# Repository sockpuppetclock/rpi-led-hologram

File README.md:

Holographic Display
==================================================
This fork adds LED controller scripts for use with a 64x64 HUB75 LED matrix as a volumetric display.
 * `startup.sh` (starts holographic-viewer, useful if set to start after boot)
 * `utils/holographic-viewer.cc` (main LED driving script)
 * `utils/holo-controller.py` & `utils/holo-autocontrol.py` (control display via zeromq)
 * `utils/img2anim.cc` (script to create .anim files from 64x64 images for holographic-viewer)

 ```bash
apt install make cmake g++ graphicsmagick-libmagick-dev-compat cppzmq-dev python3-zmq
```

Build before running:
 ```bash
 make -C utils
 make -C examples-api-use
 ```

Controlling RGB LED display with Raspberry Pi GPIO
==================================================

A library to control commonly available 64x64, 32x32 or 16x32 RGB LED panels
with the Raspberry Pi. Can support PWM up to 11Bit per channel, providing
true 24bpp color with CIE1931 profile.

Supports 3 chains with many panels each on a regular Pi.
On a Raspberry Pi 2 or 3, you can easily chain 12 panels in that chain
(so 36 panels total), but you can theoretically stretch that to up
to 96-ish panels (32 chain length) and still reach
around 100Hz refresh rate with full 24Bit color (theoretical - never tested
this; there might likely be timing problems with the panels that will creep
up then).

With fewer colors or so-called 'outdoor panels' you can control even more,
faster.

The LED-matrix library is (c) Henner Zeller <h.zeller@acm.org>, licensed with
[GNU General Public License Version 2.0 (or any later version)](http://www.gnu.org/licenses/gpl-2.0.txt)
(which means, if you use it in a product somewhere, you need to make the
source and all your modifications available to the receiver of such product so
that they have the freedom to adapt and improve). 
Yes, you are also allowed to use
this code under the [GNU General Public License Version 3.0](http://www.gnu.org/licenses/gpl-3.0.txt) 
which allows linking with Apache 2.0 code and LGPL-3.0 code.

## Discourse discussion group

**If you'd like help, please do not file a bug, use the discussion board instead:**
https://rpi-rgb-led-matrix.discourse.group/  (obviously please read this whole page first).
If you file a bug asking for personal help instead of using the discourse group, please
state in your bug that you have read this entire page and that you're indeed filing a bug
or request for improvement. Otherwise, please use the discourse group.

Overview
--------
The RGB LED matrix panels can be scored at [Sparkfun][sparkfun],
[AdaFruit][ada] or eBay and Aliexpress. If you are in China, I'd try to get
them directly from some manufacturer, Taobao or Alibaba.

The `RGBMatrix` class provided in `include/led-matrix.h` does what is needed
to control these. You can use this as a library in your own projects or just
use the demo binary provided here which provides some useful examples.

Check out [utils/ directory for some ready-made tools](./utils) to get started
using the library, or the [examples-api-use/](./examples-api-use) directory if
you want to get started programming your own utils.

Raspberry Pi up to 4 supported
------------------------------

This library supports the old Raspberry Pi's Version 1 with 26 pin header and
also the B+ models, the Pi Zero, Raspberry Pi 2 and 3 with 40 pins, as well
as the Compute Modules which have 44 GPIOs.

The Raspberry Pi 5 still needs some research into the vastly changed peripherals
and is not yet supported. See https://github.com/hzeller/rpi-rgb-led-matrix/issues/1603#issuecomment-2624713250
and https://github.com/adafruit/Adafruit_Blinka_Raspberry_Pi5_Piomatter

The 26 pin models can drive one chain of RGB panels, the 40 pin models
**up to three** chains in parallel (each chain 12 or more panels long).
The Compute Module can drive **up to 6 chains in parallel**.
The Raspberry Pi 2 and 3 are faster and generally perferred to the older
models (and the Pi Zero). With the faster models, the panels sometimes
can't keep up with the speed; check out
this [troubleshooting section](#troubleshooting) what to do.

A lightweight, non-GUI, distribution such as [DietPi] is recommended.
[Raspbian Lite][raspbian-lite] is a bit easier to get started with and
is a good second choice.

Types of Displays
-----------------
There are various types of displays that come all with the same Hub75 connector.
They vary in the way the multiplexing is happening so this library supports
options to choose that.
All these are configured by flags (or, programmatically, in an [Options struct](include/led-matrix.h#L57)).

If you have a 64x32 display, you need to supply the flags
`--led-cols=64 --led-rows=32` for instance.

Depending on the Matrix, there are various configuration options that
you might need to set for it to work. See further below in the README for the
[detailed description of these](#changing-parameters-via-command-line-flags).
While the `--led-rows` and `--led-cols` can be derived from simply looking
at the panels, the other options might require some experimenting to find the
right setting if there is no description provided by the manufacturer of
the panel. Going through these options for experiments would typically not do
harm, so you're free to experiment to find your setting.

Flag                                | Description
:---------------      | :-----------------
`--led-cols`          | Columns in the LED matrix, the 'width'.
`--led-rows`          | Rows in the LED matrix, the 'height'.
`--led-multiplexing`  | In particular bright outdoor panels with small multiplex ratios require this. Often an indicator: if there are fewer address lines than expected: ABC (instead of ABCD) for 32 high panels and ABCD (instead of ABCDE) for 64 high panels.
`--led-row-addr-type` | Adressing of rows; in particular panels with only AB address lines might indicate that this is needed.
`--led-panel-type`    | Chipset of the panel. In particular if it doesn't light up at all, you might need to play with this option because it indicates that the panel requires a particular initialization sequence.

Panels can be chained by connecting the output of one panel to the input of
the next panel. You can chain quite a few together, but the refresh rate will
reduce with longer chains.

The 64x64 matrixes typically come in two kinds: with 5 address
lines (A, B, C, D, E), or (A, B); the latter needs a `--led-row-addr-type=1`
parameter. So-called 'outdoor panels' are typically brighter and allow for
faster refresh-rate for the same size, but do some multiplexing internally
of which there are a few types out there; they can be chosen with
the `--led-multiplexing` parameter.

There are some panels that have a different chip-set than the default HUB75.
These require some initialization sequence. The current supported types are
`--led-panel-type=FM6126A` and `--led-panel-type=FM6127`.

Generally, the higher scan-rate (e.g. 1:8), a.k.a. outdoor panels generally
allow faster refresh rate, but you might need to figure out the multiplexing
mapping if one of the three provided does not work.

Some 32x16 outdoor matrixes with 1:4 scan (e.g. [Qiangli Q10(1/4) or X10(1/4)](http://qiangliled.com/products-63.html))
have 4 address line (A, B, C, D). For such matrices is necessary to
use `--led-row-addr-type=2` parameter. Also the matrix Qiangli Q10(1/4)
have "Z"-stripe pixel mapping and in this case, you'd use two parameters
at the same time `--led-row-addr-type=2 --led-multiplexing=4`.

Let's do it
------------
This documentation is split into parts that help you through the process

  1. 
    [**Wire up the matrix to your Pi**](./wiring.md). This document describes
    what goes where. You might also be interested
    in [breakout boards](./adapter) for that.
    If you have an [Adafruit HAT] or [Adafruit Bonnet], you can choose that with
    a command line option [described below](#if-you-have-an-adafruit-hat-or-bonnet)
  2. Run a demo. You find that in the
     [examples-api-use/](./examples-api-use#running-some-demos) directory:
```
make -C examples-api-use
sudo examples-api-use/demo -D0
```
  3. Use the utilities. The [utils](./utils) directory has some ready-made
    useful utilities to show content. [Go there](./utils) to see how to
    compile and run these.
  4. Write your own programs using the Matrix in C++ or one of the
     bindings such as Python or C#.

### Wiring / Boards

Please see the [Adadpter Boards or Self Wiring](./adapter). 

Summary is:
- Yes you can self wire without level shifters and it will work most of the time, but if you're not in a hurry get a board
- https://www.electrodragon.com/product/rgb-matrix-panel-drive-board-for-raspberry-pi-v2/ **is the recommended solution with 3 channels and level shifters**. You can't go wrong there, but expect a bit of shipping time.
- If shipping time is crucial and you don't want to wire your own, Adafruit sells a single channel board (the electrodragon one is 3 channels), but note that its wiring is non standard and requires a special compile option or command line argument: https://www.adafruit.com/product/3211

### Utilities

The [utils directory](./utils) is meant for ready utilities to show images or
animated gifs or videos. Read the [README](./utils/README.md) there for
instructions how to compile.

There are external projects that use this library and provide higher level
network protocols, such as the
 * [FlaschenTaschen implementation](https://github.com/hzeller/flaschen-taschen)
   (VLC can send videos to it natively)
 * [PixelPusher implementation](https://github.com/hzeller/rpi-matrix-pixelpusher) (common in light art installations)
 * [ZeroMQ-server](https://github.com/Knifa/led-matrix-zmq-server) to receive
   content.
 * Marc's [FastLED_RPIRGBPanel_GFX](http://marc.merlins.org/perso/arduino/post_2020-01-01_Running-FastLED_-Adafruit_GFX_-and-LEDMatrix-code-on-High-Resolution-RGBPanels-with-a-Raspberry-Pi.html) allows running arduino code on linux/rPi and display on bigger RGBPanel matrices than arduino chips, can.

### API

The library comes as an API that you can use for your own utilities and use-cases.

  * The native library is a C++ library (see [include/](./include)).
    Example uses you find in the [examples-api-use/](./examples-api-use)
    directory.
  * If you prefer to program in C, there is also a
    [C API](./include/led-matrix-c.h).
  * In the [python](./bindings/python) subdirectory, you find a Python API including a
    couple of [examples](./bindings/python/samples) to get started.
  * There are a couple of external bindings, such as
      * [Nodejs binding] by Maxime Journaux
      * [Nodejs/Typescript binding] by Alex Eden
      * [Go binding] by Máximo Cuadros
      * [Rust binding] by Vincent Pasquier

### Changing parameters via command-line flags

For the programs in this distribution and also automatically in your own
programs using this library, there are a lot of parameters provided as command
line flags, so that you don't have to re-compile your programs to tweak them.
Some might need to be changed for your particular kind of panel.

Here is a little run-down of what these command-line flags do and when you'd
like to change them.

First things first: if you have a different wiring than described in
[wiring](./wiring.md), for instance if you have an Adafruit HAT/Bonnet, you can
choose these here:

```
--led-gpio-mapping=<gpio-mapping>: Name of GPIO mapping used. Default "regular"
```

This can have values such as
  - `--led-gpio-mapping=regular` The standard mapping of this library, described in the [wiring](./wiring.md) page.
  - `--led-gpio-mapping=adafruit-hat` The Adafruit HAT/Bonnet, that uses this library or
  - `--led-gpio-mapping=adafruit-hat-pwm` Adafruit HAT with the anti-flicker hardware mod [described below](#improving-flicker).
  - `--led-gpio-mapping=compute-module` Additional 3 parallel chains can be used with the Compute Module.

Learn more about the mappings in the [wiring documentation](wiring.md#alternative-hardware-mappings).

#### GPIO speed

```
--led-slowdown-gpio=<0..4>: Slowdown GPIO. Needed for faster Pis and/or slower panels (Default: 1).
```

The Raspberry Pi starting with Pi2 are putting out data too fast for almost
all LED panels I have seen. In this case, you want to slow down writing to
GPIO. Zero for this parameter means 'no slowdown'.

The default 1 (one) typically works fine, but often you have to even go further
by setting it to 2 (two). If you have a Raspberry Pi with a slower processor
(Model A, A+, B+, Zero), then a value of 0 (zero) might work and is desirable.

A Raspberry Pi 3 or Pi4 might even need higher values for the panels to be
happy.

#### Panel Connection
The next most important flags describe the type and number of displays connected

```
--led-rows=<rows>        : Panel rows. Typically 8, 16, 32 or 64. (Default: 32).
--led-cols=<cols>        : Panel columns. Typically 32 or 64. (Default: 32).
--led-chain=<chained>    : Number of daisy-chained panels. (Default: 1).
--led-parallel=<parallel>: For A/B+ models or RPi2,3b: parallel chains. range=1..3 (Default: 1, 6 for Compute Module).
```

These are the most important ones: here you choose how many panels you have
connected and how many rows are in each panel. Panels can be chained (each panel
has an input and output connector, see the
[wiring documentation](wiring.md#chains)) -- the `--led-chain` flag tells the
library how many panels are chained together. The newer Raspberry Pi's allow
to connect multiple chains in parallel, the `--led-parallel` flag tells it how
many there are.

This illustrates what each of these parameters mean:

##### Panel Type

Typically, panels should just work out of the box, but some panels use a
different chip-set that requires some initialization. If you don't see any
output on your panel, try setting:

```
--led-panel-type=FM6126A
```

Some panels have the FM6127 chip, which is also an option.

##### Multiplexing
If you have some 'outdoor' panels or panels with different multiplexing,
the following will be useful:

```
--led-multiplexing=<0..17> : Mux type: 0=direct; 1=Stripe; 2=Checkered...
```

The outdoor panels have different multiplexing which allows them to be faster
and brighter, but by default their output looks jumbled up.
They require some pixel-mapping of which there are a few
types you can try and hopefully one of them works for your panel; The default=0
is no mapping ('standard' panels), while 1, 2, ... are different mappings
to try with. If your panel has a different mapping, you find everything you
need to implement one in [lib/multiplex-mappers.cc](lib/multiplex-mappers.cc).
Please send a pull request if you encounter a panel for which you needed to
implement a new mapping.

Note that you have to set the `--led-rows` and `--led-cols` to the rows and
columns that are physically on each chained panel so that the multiplexing
option can work properly. For instance a `32x16` panel with `1:4` multiplexing
would be controlled with `--led-rows=16 --led-cols=32 --led-multiplexing=1` (or
whatever multiplexing type your panel is, so it can also be `--led-multiplexing=2` ...).

For `64x32` panels with `1:8` multiplexing, this would typically be
`--led-rows=32 --led-cols=64 --led-multiplexing=1`;
however, there are some panels that internally behave like
two chained panels, so then you'd use
`--led-rows=32 --led-cols=32 --led-chain=2 --led-multiplexing=1`;

```
--led-row-addr-type=<0..4>: 0 = default; 1 = AB-addressed panels; 2 = direct row select; 3 = ABC-addressed panels; 4 = ABC Shift + DE direct (Default: 0).
```

This option is useful for certain 64x64 or 32x16 panels. For 64x64 panels,
that only have an `A` and `B` address line, you'd use `--led-row-addr-type=1`.
This is only tested with one panel so far, so if it doesn't work for you,
please send a pull request.

For 32x16 outdoor panels, that have have 4 address line (A, B, C, D), it is
necessary to use `--led-row-addr-type=2`.

#### Panel Arrangement

```
--led-pixel-mapper  : Semicolon-separated list of pixel-mappers to arrange pixels.
```

Optional params after a colon e.g. "U-mapper;Rotate:90"

Available | Parameter after colon| Example
----------|----------------------|----------
Mirror    | `H` or `V` for horizontal/vertical mirror. | `Mirror:H`
Rotate    | Degrees.                                   | `Rotate:90`
U-mapper  | -

Mapping the logical layout of your boards to your physical arrangement. See
more in [Remapping coordinates](./examples-api-use#remapping-coordinates).

#### Misc Options

```
--led-brightness=<percent>: Brightness in percent (Default: 100).
```

Self explanatory.

```
--led-pwm-bits=<1..11>    : PWM bits (Default: 11).
```

The LEDs can only be switched on or off, so the shaded brightness perception
is achieved via PWM (Pulse Width Modulation). In order to get a good 8 Bit
per color resolution (24Bit RGB), the 11 bits default per color are good
(why ? Because our eyes are actually perceiving brightness logarithmically, so
we need a lot more physical resolution to get 24Bit sRGB).

With this flag, you can change how many bits it should use for this; lowering it
means the lower bits (=more subtle color nuances) are omitted.
Typically you might be mostly interested in the extremes: 1 Bit for situations
that only require 8 colors (e.g. for high contrast text displays) or 11 Bit
for everything else (e.g. showing images or videos). Why would you bother at all ?
Lower number of bits use slightly less CPU and result in a higher refresh rate.

```
--led-show-refresh        : Show refresh rate.
```

This shows the current refresh rate of the LED panel, the time to refresh
a full picture. Typically, you want this number to be pretty high, because the
human eye is pretty sensitive to flicker. Depending on the settings, the
refresh rate with this library are typically in the hundreds of Hertz but
can drop low with very long chains. Humans have different levels of perceiving
flicker - some are fine with 100Hz refresh, others need 250Hz.
So if you are curious, this gives you the number (shown on the terminal).

The refresh rate depends on a lot of factors, from `--led-rows` and `--led-chain`
to `--led-pwm-bits`, `--led-pwm-lsb-nanoseconds` and `--led-pwm-dither-bits`.
If you are tweaking these parameters, showing the refresh rate can be a
useful tool.

```
--led-limit-refresh=<Hz>  : Limit refresh rate to this frequency in Hz. Useful to keep a
                            constant refresh rate on loaded system. 0=no limit. Default: 0
```

This allows to limit the refresh rate to a particular frequency to approach
a fixed refresh rate.

This can be used to mitigate some situations in which you have a faint flicker,
which can happen due to hardware events (network access)
or other situations such as other IO or heavy memory access by other
processes. Also when you see wildly changing refresh frequencies with
`--led-show-refresh`.

You trade a slightly slower refresh rate and display brightness for less
visible flicker situations.

For this to calibrate, run your program for a while with --led-show-refresh
and watch the line that shows the current refresh rate and minimum refresh
rate observed. So wait a while until that value doesn't
change anymore (e.g. a minute, so that you catch tasks that happen once
a minute, such as ntp updated).
Use this as a guidance what value to choose with `--led-limit-refresh`.

The refresh rate will now be adapted to always reach this value
between frames, so faster refreshes will be slowed down, but the occasional
delayed frame will fit into the time-window as well, thus reducing visible
brightness fluctuations.

You can play with value a little and reduce until you find a good balance
between refresh rate and flicker suppression.

Use this also if you want to have a stable baseline refresh rate when using
the vsync-multiple flag `-V` in the [led-image-viewer] or
[video-viewer] utility programs.

```
--led-no-busy-waiting     : Don't use busy waiting when limiting refresh rate.
```

This allows to switch from busy waiting to sleep waiting when limiting the
refresh rate (`--led-limit-refresh`).

By default, refresh rate limiting uses busy waiting, which is CPU intensive but
gives most accurate timings. This is fine for multi-core boards.

On single core boards (e.g.: Raspberry Pi Zero) busy waiting makes the system
unresponsive for other/background tasks. There, sleep waiting improves the
system's responsiveness at the cost of slightly less accurate timings.

```
--led-scan-mode=<0..1>    : 0 = progressive; 1 = interlaced (Default: 0).
```

This switches from progressive scan and interlaced scan. The latter might
look be a little nicer when you have a very low refresh rate, but typically
it is more annoying because of the comb-effect (remember 80ies TV ?).

```
--led-pwm-lsb-nanoseconds : PWM Nanoseconds for LSB (Default: 130)
```

This allows to change the base time-unit for the on-time in the lowest
significant bit in nanoseconds.
Lower values will allow higher frame-rate, but will also negatively impact
qualty in some panels (less accurate color or more ghosting).

Good values for full-color display (PWM=11) are somewhere between 100 and 300.

If you you use reduced bit color (e.g. PWM=1) and have sharp contrast
applications, then higher values might be good to minimize ghosting.

How to decide ? Just leave the default if things are fine. But some panels have
trouble with sharp contrasts and short pulses that results
in ghosting. It is particularly apparent in situations such as bright text
on black background. In these cases increase the value until you don't see
this ghosting anymore.

The following example shows how this might look like:

Ghosting with low --led-pwm-lsb-nanoseconds  | No ghosting after tweaking
---------------------------------------------|------------------------------
                   |

If you tweak this value, watch the framerate (`--led-show-refresh`) while playing
with this number.

```
--led-pwm-dither-bits   : Time dithering of lower bits (Default: 0)
```

The lower bits can be time dithered, i.e. their brightness contribution is
achieved by only showing them some frames (this is possible,
because the PWM is implemented as binary code modulation).
This will allow higher refresh rate (or same refresh rate with increased
`--led-pwm-lsb-nanoseconds`).
The disadvantage could be slightly lower brightness, in particular for longer
chains, and higher CPU use.
CPU use is not of concern for Rasbperry Pi 2 or 3 (as we run on a dedicated
core anyway) but proably for Raspberry Pi 1 or Pi Zero.
Default: no dithering; if you have a Pi 3 and struggle with low frame-rate due
to high multiplexing panels (1:16 or 1:32) or long chains, it might be
worthwhile to try.

```
--led-no-hardware-pulse   : Don't use hardware pin-pulse generation.
```

This library uses a hardware subsystem that also is used by the sound. You can't
use them together. If your panel does not work, this might be a good start
to debug if it has something to do with the sound subsystem (see Troubleshooting
section). This is really only recommended for debugging; typically you actually
want the hardware pulses as it results in a much more stable picture.

```
--led-no-drop-privs       : Don't drop privileges from 'root' after initializing the hardware.
```

You need to start programs as root as it needs to access some low-level hardware
at initialization time. After that, it is typically not desirable to stay in this
role, so the library then drops the privileges.

This flag allows to switch off this behavior, so that you stay root.
Not recommended unless you have a specific reason for it (e.g. you need root
to access other hardware or you do the privilege dropping yourself).

```
--led-daemon              : Make the process run in the background as daemon.
```

If this is set, the program puts itself into the background (running
as 'daemon').
You might want this if started from an init script at boot-time.

```
--led-inverse             : Switch if your matrix has inverse colors on.
--led-rgb-sequence        : Switch if your matrix has led colors swapped (Default: "RGB")
```

These are if you have a different kind of LED panel in which the logic of the
color bits is reversed (`--led-inverse`) or where the Red, Green and Blue LEDs
are mixed up (`--led-rgb-sequence`). You know it when you see it.

Troubleshooting
---------------
Here are some tips in case things don't work as expected.

### Use minimal Raspbian distribution
In general, run a minimal configuration on your Pi.

  * Do not use a graphical user interface (Even though the
    Raspberry Pi foundation makes you believe that you can do that: don't.
    Using a Pi with a GUI is a frustratingly slow use of an otherwise
    perfectly good embedded device.).
    Always operate your Raspberry Pi [headless].

  * Switch off on-board sound
    (`dtparam=audio=off` in `/boot/config.txt` pre-bookworm)
    (`dtparam=audio=off` in `/boot/firmware/config.txt` post-bookworm)
    External USB sound adapters work, and are much better quality anyway,
    so that is recommended if you happen to need sound. The on-board sound
    uses a timing circuit that the RGB-Matrix needs (it seems in some
    distributions, such as arch-linux, this is not enough and you need
    to explicitly blacklist the snd_bcm2835 module).

  * Don't run anything that messes in parallel with the GPIO pins, e.g.
    PiGPIO library/daemon or devices that use the i2c or 1-wire interface if
    they are on the same pins you need for the panel.

  * I have also seen reports that on some Pis, the one-wire protocol is
    enabled (w1-gpio). This will also not work (disable by removing
    `dtoverlay=w1-gpio` in `/boot/config.txt` (pre-bookworm) or in
    `/boot/firmware/config.txt` (post-bookworm); or using `raspi-config`,
    Interface Options -> 1-Wire)

  * If you see some regular flickering, make sure that there is no other
    process running on the system that could cause that. For instance, it is
    known that merely running `top` creates a faint flicker every second it
    updates. Or a regular ntp run can also cause flicker once a minute
    (switch off with `sudo timedatectl set-ntp false`). Maybe instead you
    might want to run ntp at system start-up but then not regularly updating.
    There might be other things running regularly you don't need;
    consider a `sudo systemctl stop cron` for instance.
    To address some irregular flicker, consider the
    [`--led-limit-refresh`](#misc-options) option.

  * There are probably other processes that are running that you don't need
    and remove them; I usually remove right away stuff I really don't need e.g.
    ```
    sudo apt-get remove bluez bluez-firmware pi-bluetooth triggerhappy pigpio
    ```
    Take a close look at your systemd (`systemctl`) and see if there are other
    things running you don't need. If you have seen packages in standard
    Raspbians that interfere with the matrix code, let me know to include it
    here.
    In general: This is why starting with a minimal installation is a good
    idea: there is simply less cruft that you have to disable.

  * It seems that more recent version of Raspbian Lite result in some faint
    brightness fluctuations of the displays and it is not quite clear why (see
    issue [#483](https://github.com/hzeller/rpi-rgb-led-matrix/issues/483)).
    If you are a Kernel person and can help figuring out what is
    happening that would be very appreciated. Also, you might know a minimal
    Linux distribution that is more suited for near realtime applications ?

The default install of **[Raspbian Lite][raspbian-lite]** or **[DietPi]**
seem to be good starting points, as they have a reasonably minimal
configuration to begin with. Raspbian Lite is not as lite anymore
as it used to be; I prefer DietPi these days.

### Bad interaction with Sound
If sound is enabled on your Pi, this will not work together with the LED matrix,
as both need the same internal hardware sub-system (a first test to see if you
are affected is to run the progrem with `--led-no-hardware-pulse` and see if
things work fine then).

If you run `lsmod` and see the `snd_bcm2835` module, this could be causing trouble.
(The library actually exits if it finds this module to be loaded).

In that case, you should create a kernel module blacklist file like the
following on your system and update your initramfs:

```
cat <<EOF | sudo tee /etc/modprobe.d/blacklist-rgb-matrix.conf
blacklist snd_bcm2835
EOF

sudo update-initramfs -u
```

Reboot and confirm that the module is not loaded.

### I have followed some tutorial on the Internet and it doesn't work

Well, if you use this library, please read the documentation provided _here_,
not on some other website. Most important for you to get started
is the [wiring guide](./wiring.md). There are some tutorials floating around
that refer to a very old version of this library.

### I have a Pi1 Revision1 and top part of Panel doesn't show green

Use `--led-gpio-mapping=regular-pi1`

### Logic level voltage not sufficient
Some panels don't interpret the 3.3V logic level well, or the RPi output drivers
have trouble driving longer cables, in particular with
faster Raspberry Pis Version 2. This results in artifacts like randomly
showing up pixels, color fringes, or parts of the panel showing 'static'.

If you encounter this, try these things

   - Make sure to have as short as possible flat-cables connecting your
     Raspberry Pi with the LED panel.

   - In particular if the chips close to the input of the LED panel
     read 74HC245 instead of 74HCT245 or 74AHCT245, then this board will not
     work properly with 3.3V inputs coming from the Pi.
     Use an [adapter board](./adapter/active-3) with a bus-driver that acts as
     level shifter between 3.3V and 5V.
     (In any case, it is always a good idea to use the level shifters).

   - A temporary hack to make HC245 inputs work with the 3.3V levels is to
     supply only like 4V to the LED panel. But the colors will be off, so not
     really useable as long-term solution.

   - If you can't implement the above things, or still have problems, you can
     slow down the GPIO writing a bit. This will of course reduce the
     frame-rate, so it comes at a cost.

For GPIO slow-down, add the flag `--led-slowdown-gpio=2` to the invocation of
the binary.

If you have an Adafruit HAT or Bonnet
---------------------------

Generally, if you want to connect RGB panels via an adapter instead of
hand-wiring, I suggest to build one of the adapters whose open-hardware
files you find in the [adapter/](./adapter) subdirectory. It is a fun solder
exercise with large surface mount components.

However, Adafruit [offers an adapter][adafruit-hat] which is already ready-made,
but it only allows for a single chain. If the
ready-made vs. single-chain tradeoff is worthwhile, then you might go for that
(I am not affiliated with Adafruit).

### Switch the Pinout

The Adafruit HAT/Bonnet uses this library but a modified pinout to support other
features on the HAT. You can choose the Adafruit pinout with a command line
flag.

Just pass the option `--led-gpio-mapping=adafruit-hat`. This works on the C++
and Python examples.

### Improving flicker

To improve flicker, we need to do a little hardware modification,
but it is very simple: solder a wire between GPIO 4 and 18 as shown in the
following picture (click to enlarge):

Then, start your programs with `--led-gpio-mapping=adafruit-hat-pwm`.

Now you should have less visible flicker. This essentially
switches on the hardware pulses feature for the Adafruit HAT/Bonnet.

### 64x64 with E-line on Adafruit HAT/Bonnet
There are LED panels that have 64x64 LEDs packed, but they need 5 address lines,
which is 1:32 multiplexing (they have an `E` address-line). The first generation
of the Adafruit HAT/Bonnet was not prepared for this, but it can be done with another
hardware mod. Beginning October 2018, Adafruit began selling an updated version of
the HAT that supports 64x64 panels simply by bridging two pads on the PCB with solder.

You can identify which HAT you have by looking for the **Address E** pads, circled here:

### New Adafruit RGB Matrix Hat (with Address E pads)

Look for the Address E pads located between the HUB75 connector and Pi camera cutout.

Melt a blob of solder between the center “E” pad the the “8” pad just above it
(for 64x64 matrices in the Adafruit shop)…*_or_* the “16” pad below (rare, for some
third-party 64x64 matrices…check datasheet).

### Old Adafruit HAT/Bonnet (without)

It is a little more advanced hack, so it is only really for people who are
comfortable with this kind of thing.
First, you have to figure out which is the input of the E-Line on your matrix
(they seem to be either on Pin 4 or Pin 8 of the IDC connector).
You need to disconnect that Pin from the ground plane (e.g. with an Exacto
knife) and connect GPIO 24 to it. The following images illustrate the case for
IDC Pin 4.

If the direct connection does not work, you need to send it through a free
level converter of the Adafruit HAT/Bonnet. Since all unused inputs are grounded
with traces under the chip, this involves lifting a leg from the
HCT245 (figure out a free bus driver from the schematic). If all of the
above makes sense to you, you have the Ninja level to do it!

It might be more convienent at this point to consider the [Active3 adapter](./adapter/active-3)
that has that covered already.

Running as root
---------------
The library requires to access hardware registers to control the LED matrix,
and create accurate timings. These hardware accesses require to run as root
user.

For security reasons, it is usually not a good idea to run an application
as root entirely, so this library makes sure to drop privileges immediately
after the hardware is initialized.

You can switch off the privilege dropping with the
[`--led-no-drop-privs`](#user-content-no-drop-priv) flag, or, if you do this
programmatically,
choose the configuration in the
[`RuntimeOptions struct`](https://github.com/hzeller/rpi-rgb-led-matrix/blob/master/include/led-matrix.h#L401).

Note, you _could_ run as non-root, which will use `/dev/gpiomem`
to at least write to GPIO, however the precise timing hardware registers are
not accessible. This will result in flicker and color degradation. Starting
as non-root is not recommended.

CPU use
-------

These displays need to be updated constantly to show an image with PWMed
LEDs. This is dependent on the length of the chain: for each chain element,
about 1'000'000 write operations have to happen every second!
(chain_length * 32 pixel long * 16 rows * 11 bit planes * 180 Hz refresh rate).

We can't use hardware support for writing these as DMA is too slow,
thus the constant CPU use on an RPi is roughly 30-40% of one core.
Keep that in mind if you plan to run other things on this computer (This
is less noticable on Raspberry Pi, Version 2 or 3 that has more cores).

Also, the output quality is susceptible to other heavy tasks running on that
computer - there might be changes in the overall brigthness when this affects
the referesh rate.

If you have a loaded system and one of the newer Pis with 4 cores, you can
reserve one core just for the refresh of the display. Add:

```
isolcpus=3
```

to the end of the line in `/boot/cmdline.txt` (pre-bookworm) or
`boot/firmware/cmdline.txt` (post-bookworm). It needs to be in the same line
line as the existing arguments -- no newline. This will use the last core
only to refresh the display then, but it also means, that no other process can
utilize it then. Still, I'd typically recommend it.

Performance improvements and limits
-----------------------------------
Regardless of which driving hardware you use, ultimately you can only push pixels
so fast to a string of panels before you get flickering due to too low a refresh
rate (less than 80-100Hz), or before you refresh the panel lines too fast and they
appear too dim because each line is not displayed long enough before it is turned off.

Basic performance tips:
- Use --led-show-refresh to see the refresh rate while you try parameters
- use an active-3 board with led-parallel=3
- led-pwm-dither-bits=1 gives you a speed boost but less brightness
- led-pwm-lsb-nanoseconds=50 also gives you a speed boost but less brightness
- led-pwm-bits=7 or even lower decrease color depth but increases refresh speed
- AB panels and other panels with that use values of led-multiplexing bigger than 0,
will also go faster, although as you tune more options given above, their advantage will decrease.
- 32x16 ABC panels are faster than ABCD which are faster than ABCDE, which are faster than 128x64 ABC panels
(which do use 5 address lines, but over only 3 wires)
- Use at least an rPi3 (rPi4 is still slightly faster but may need --led-slowdown-gpio=2)

Maximum resolutions reasonably achievable:
A general rule of thumb is that running 16K pixels (128x128 or otherwise) on a single chain,
is already pushing limits and you will have to make tradeoffs in visual quality. 32K pixels
(like 128x256) is definitely pushing things and you'll get 100Hz or less depending on the
performance options you choose.
This puts the maximum reasonable resolution around 100K pixels (like 384x256) for 3 chains.
You can see more examples and video capture of speed on [Marc MERLIN's page 'RGB Panels, from 192x80, to 384x192, to 384x256 and maybe not much beyond'](http://marc.merlins.org/perso/arduino/post_2020-03-13_RGB-Panels_-from-192x80_-to-384x192_-to-384x256-and-maybe-not-much-beyond.html)
If your refresh rate is below 300Hz, expect likely black bars when taking cell phone pictures.
A real camera with shutter speed lowered accordingly, will get around this.

Ultimately, you should not expect to go past 64K pixels using 3 chains without significant
quality tradeoffs. If you need bigger displays, you should use multiple boards and synchronize the
output.

Limitations
-----------
If you are using the Adafruit HAT/Bonnet in the default configuration, then we
can't make use of the PWM hardware (which only outputs
to a particular pin), so you'll see random brightness glitches. I strongly
suggest to do the aforementioned hardware mod.

The system needs constant CPU to update the display. Using the DMA controller
was considered but after extensive experiments
( https://github.com/hzeller/rpi-gpio-dma-demo )
dropped due to its slow speed..

There is an upper limit in how fast the GPIO pins can be controlled, which
limits the frame-rate. Raspberry Pi 2's and newer are generally faster.

Even with everything in place, you might see faint brightness fluctuations
in particular if there is something going on on the network or in a terminal
on the Pi; this could probably be mitigated with some more real-time
kernel for the Pi; maybe there are also hardware limitations (memory bus
contention?). Anyway, if you have a realtime kernel configuration that you
have optimized for this application, let me know.

To address the brightness fluctuations, you might experiment with the
`FIXED_FRAME_MICROSECONDS` compile time option in [lib/Makefile](lib/Makefile)
that has instructions how to set it up.

Fun
---
I am always happy to see users successfully using the software for wonderful
things, like this installation by Dirk in Scharbeutz, Germany:

[led-image-viewer]: ./utils#image-viewer
[video-viewer]: ./utils#video-viewer
[matrix64]: ./img/chained-64x64.jpg
[sparkfun]: https://www.sparkfun.com/products/12584
[ada]: http://www.adafruit.com/product/1484
[rt-paper]: https://www.osadl.org/fileadmin/dam/rtlws/12/Brown.pdf
[adafruit-hat]: https://www.adafruit.com/products/2345
[raspbian-lite]: https://downloads.raspberrypi.org/raspbian_lite_latest
[DietPi]: https://dietpi.com/
[Adafruit HAT]: https://www.adafruit.com/products/2345
[Adafruit Bonnet]: https://www.adafruit.com/product/3211
[Nodejs binding]: https://github.com/zeitungen/node-rpi-rgb-led-matrix
[Go binding]: https://github.com/mcuadros/go-rpi-rgb-led-matrix
[Rust binding]: https://crates.io/crates/rpi-led-matrix
[Nodejs/Typescript binding]: https://github.com/alexeden/rpi-led-matrix
[headless]: https://www.raspberrypi.com/documentation/computers/configuration.html#setting-up-a-headless-raspberry-pi

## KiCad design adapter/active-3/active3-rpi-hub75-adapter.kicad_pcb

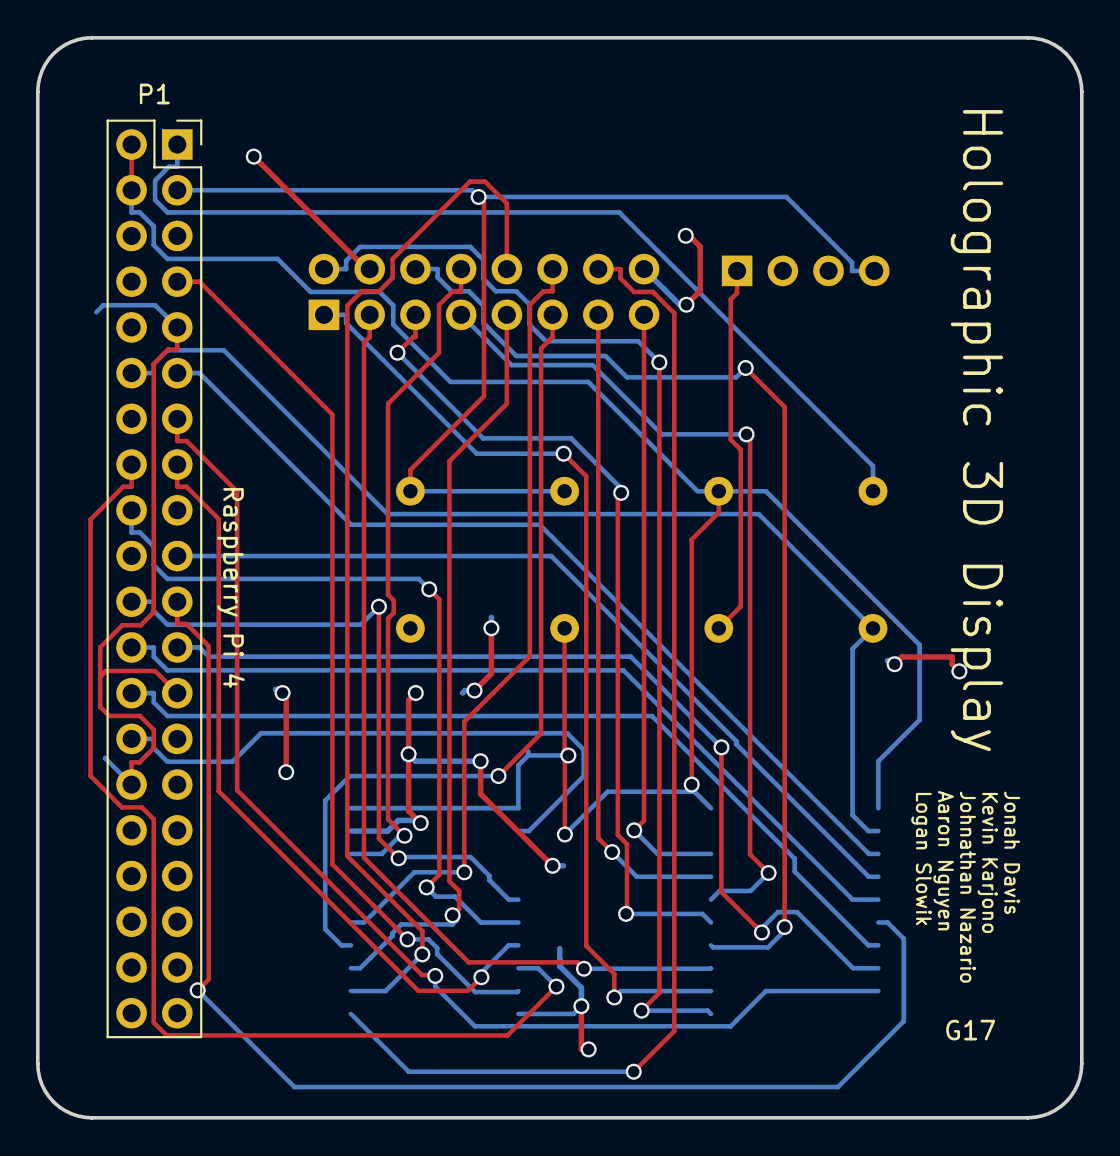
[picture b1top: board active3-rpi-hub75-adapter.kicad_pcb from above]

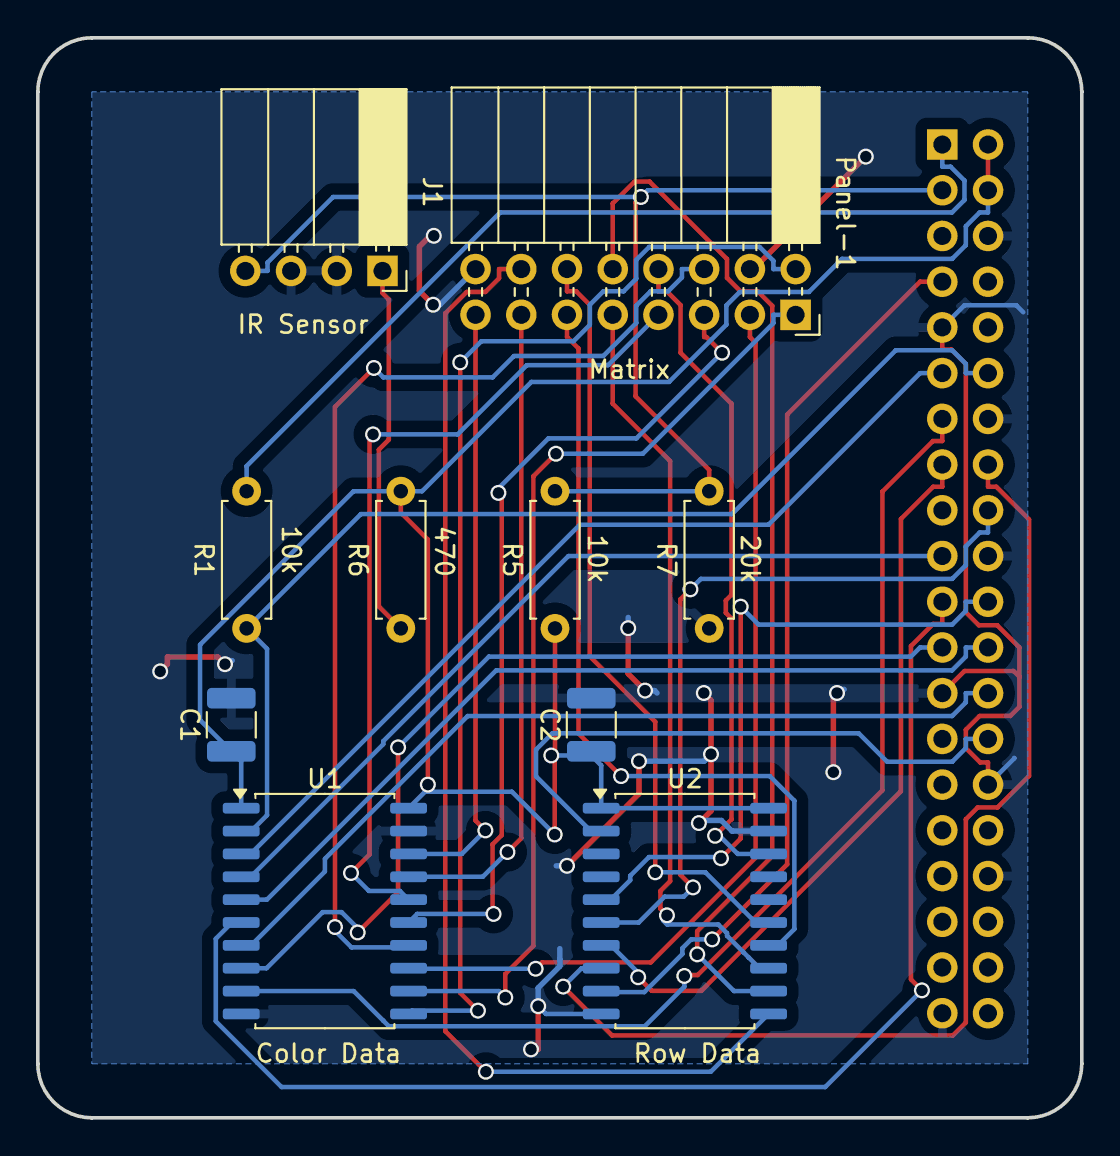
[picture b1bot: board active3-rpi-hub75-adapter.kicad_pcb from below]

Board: 2 copper layers, 58.0 x 60.0 mm, 11 parts (10 on the bottom side), 33 nets.

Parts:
C1, C2: 100n; C_1210_3225Metric
J1: IR_Sensor_Socket; PinSocket_1x04_P2.54mm_Horizontal
P1: CONN_02X20; PinSocket_2x20_P2.54mm_Vertical
Panel-1: CONN_02X08; PinSocket_2x08_P2.54mm_Horizontal
R1, R5: 10k; R_Axial_DIN0207_L6.3mm_D2.5mm_P7.62mm_Horizontal
R6: 470; R_Axial_DIN0207_L6.3mm_D2.5mm_P7.62mm_Horizontal
R7: 20k; R_Axial_DIN0207_L6.3mm_D2.5mm_P7.62mm_Horizontal
U1, U2: 74HCT245; SOIC-20W_7.5x12.8mm_P1.27mm

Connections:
GND: C1.2, C2.2, J1.2, J1.3, P1.6, P1.9, P1.14, P1.20, P1.25, P1.30, P1.34, P1.39, Panel-1.4, Panel-1.16, R7.1, U1.10 (GND), U1.19 (CE), U2.10 (GND), U2.19 (CE)
unnamed: J1.1, R6.1
unnamed: P1.1, R1.2
OE: P1.12, R1.1, U1.2 (A0)
OE_buff_0: Panel-1.15, U1.18 (B0)
VCC: C1.1, C2.1, P1.2, P1.4, R5.1, R6.2, U1.1 (A->B), U1.20 (VCC), U2.1 (A->B), U2.20 (VCC)
clock: P1.11, U1.3 (A1)
clock_buff_0: Panel-1.13, U1.17 (B1)
p0_b1: P1.26, U1.7 (A5)
p0_b1_buff: Panel-1.3, U1.13 (B5)
p0_b2: P1.19, U1.4 (A2)
p0_b2_buff: Panel-1.7, U1.16 (B2)
p0_g1: P1.13, U1.9 (A7)
p0_g1_buff: Panel-1.2, U1.11 (B7)
p0_g2: P1.21, U1.6 (A4)
p0_g2_buff: Panel-1.6, U1.14 (B4)
p0_r1: P1.23, U1.8 (A6)
p0_r1_buff: Panel-1.1, U1.12 (B6)
p0_r2: P1.24, U1.5 (A3)
p0_r2_buff: Panel-1.5, U1.15 (B3)
row_A: P1.15, U2.7 (A5)
row_A_buff: Panel-1.9, U2.13 (B5)
row_B: P1.16, U2.8 (A6)
row_B_buff: Panel-1.10, U2.12 (B6)
row_C: P1.18, U2.6 (A4)
row_C_buff: Panel-1.11, U2.14 (B4)
row_D: P1.22, U2.5 (A3)
row_D_buff: Panel-1.12, U2.15 (B3)
row_E: P1.28, U2.2 (A0)
row_E_buff: Panel-1.8, U2.18 (B0)
spin_sync: J1.4, P1.3, R5.2, R7.2
strobe: P1.7, U2.9 (A7)
strobe_buff_0: Panel-1.14, U2.11 (B7)

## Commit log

2025-04-23 initial uart code & hologram gpio
2025-04-24 Forks viewing process to background. Kills old one when new one arrives
2025-04-24 uart code can change states, updated gitignore
2025-04-24 actually fixed gitignore
2025-04-25 spin sync & signal-switching uart code
2025-04-28 receive swipe
2025-04-29 split led-image-viewer to hologram-viewer, starting to integrate uart into c code
2025-04-29 uart communication in c
2025-04-30 lotta uart work
2025-04-30 more work
2025-04-30 better pthreading
2025-04-30 moved to /hologram and better uart
2025-04-30 default idle images
2025-04-30 uart actually working
2025-04-30 adjustments
2025-04-30 rotation measuring
2025-05-01 hologram uart controller instead of uart in cpp
2025-05-02 zeromq implementation
2025-05-02 filename state splitting progress
2025-05-03 more
2025-05-03 fix row bit
2025-05-03 oh my god
2025-05-03 Update hologram-viewer.cc
    migu
2025-05-03 Update hologram-uart.py
    more migu
2025-05-03 first test
2025-05-03 first test 2
2025-05-03 bug progress
2025-05-03 it worked
2025-06-28 startup script
2025-07-11 uart work
2025-07-29 .anim files and reorganzing code
2025-07-29 zeromq and left/right rotation offset
2025-08-02 hologram can animate
2025-08-02 hologram auto controller + touch communication
2025-08-02 auto controller : update ip from file while running
2025-08-02 cleanup and documentation
2025-08-11 quick startup
2025-08-11 smoother rotation and anim resets properly. new anims directory. image-to-rgb sets loop to end by default
2025-08-11 better auto controller
2025-08-11 renamed files
2025-08-11 attempt to fix bad_alloc
2025-08-11 new idle
2025-08-11 more fixing, renamed image-to-rgb > img2anim
2025-08-11 reworking file reading
2025-08-11 added schematic edits
2025-08-12 newer schematics
2025-08-12 fixed readme names
2025-08-12 more file reading work
2025-08-12 it works but it's slow
2025-08-12 startup fix. switch file reading to mmap
2025-08-12 reverting hologram-viewer until i get a better idea
2025-08-12 direct paths in startup script
2025-08-12 .gitignore
2025-08-12 working real-time threaded file streaming. im a genius
2025-08-12 moved font files
